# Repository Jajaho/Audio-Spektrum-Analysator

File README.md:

# Audio-Spektrum-Analysator
Analog audio spectrum analyzer with bar graph display.

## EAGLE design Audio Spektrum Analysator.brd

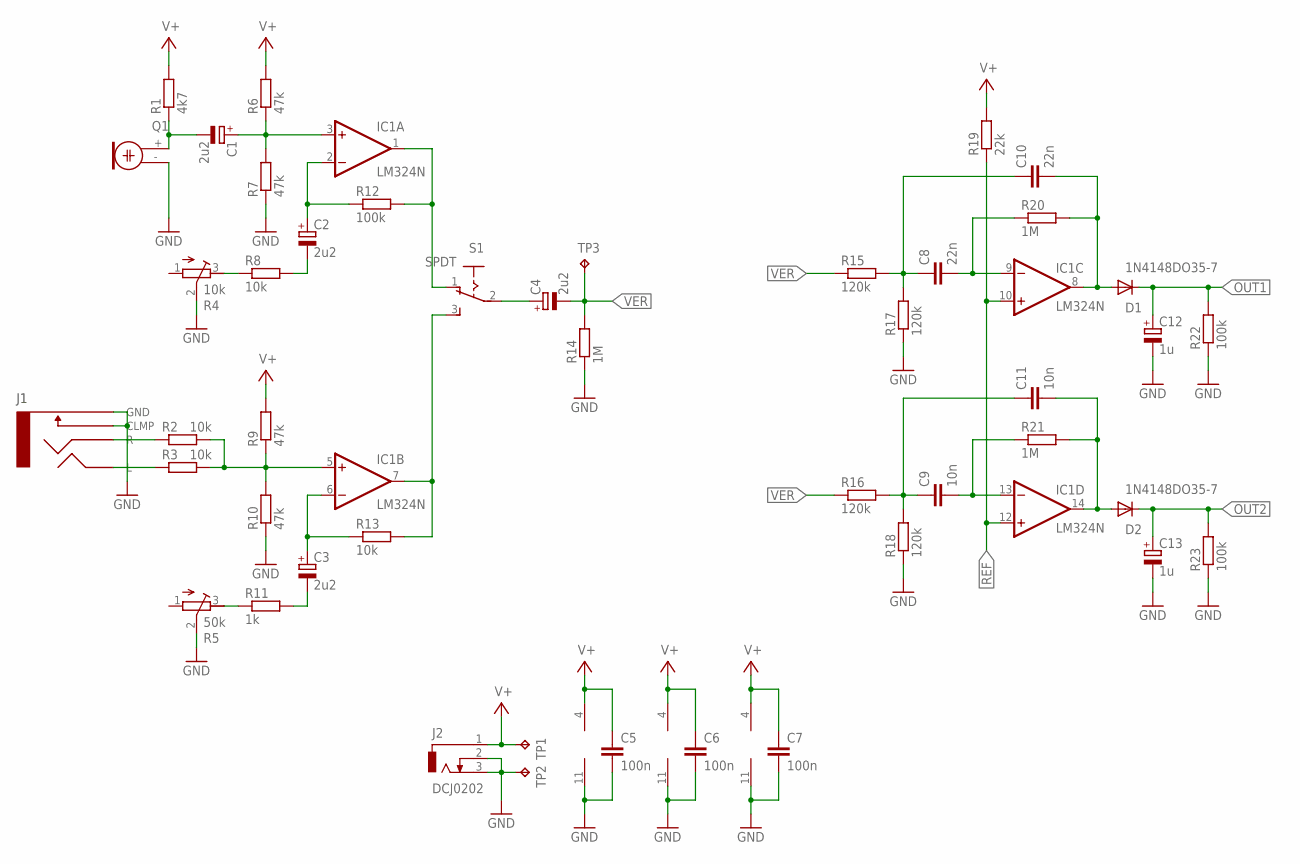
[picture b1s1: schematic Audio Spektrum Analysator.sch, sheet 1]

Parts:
C1, C2, C3, C4: 2u2; E2,5-5
C5, C6, C7: 100n; C050-024X044
C8, C10: 22n; C025-024X044
C9, C11: 10n; C025-024X044
C12, C13: 1u; E2,5-5
D1, D2: 1N4148DO35-7; DO35-7
IC1, IC2, IC3: LM324N; DIL14
J1: 2.5MM-AUXS; 2,5MM-AUX_JACK
J2: DCJ0202
Q1: ELECTRET; 9.7ELECTRET
R1: 4k7; 0207/7
R2, R3, R8, R13: 10k; 0207/7
R4: 10k; RTRIM64W
R5: 50k; RTRIM64W
R6, R7, R9, R10: 47k; 0207/7
R11: 1k; 0207/7
R12, R22, R23: 100k; 0207/7
R14, R20, R21: 1M; 0207/7
R15, R16, R17, R18: 120k; 0207/7
R19: 22k; 0207/7
S1: SPDT
TP1, TP2, TP3: TPPAD1-20; P1-20

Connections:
GND: C5.2, C6.2, C7.2, C12.-, C13.-, IC1.11 (V-), IC2.11 (V-), IC3.11 (V-), J1.1 (GND), J1.4 (CLMP), J2.2, J2.3, Q1.- (1), R4.2 (S), R5.2 (S), R7.1, R10.1, R14.1, R17.1, R18.1, R22.1, R23.1, TP2.TP; also elsewhere on the board
unnamed: J1.2 (R), R2.1
unnamed: J1.3 (L), R3.1
unnamed: IC1.5 (+IN), R2.2, R3.2, R9.1, R10.2
unnamed: C1.+, IC1.3 (+IN), R6.1, R7.2
unnamed: C2.+, IC1.2 (-IN), R12.1
unnamed: IC1.1 (OUT), R12.2, S1.1
unnamed: IC1.7 (OUT), R13.2, S1.3
unnamed: C4.+, S1.2
unnamed: C1.-, Q1.+ (2), R1.1
unnamed: C2.-, R8.2
unnamed: R4.3 (E), R8.1
unnamed: C3.+, IC1.6 (-IN), R13.1
unnamed: C3.-, R11.2
unnamed: R5.3 (E), R11.1
unnamed: C10.2, D1.A, IC1.8 (OUT), R20.2
unnamed: C8.2, IC1.9 (-IN), R20.1
unnamed: C8.1, C10.1, R15.2, R17.2
unnamed: C11.2, D2.A, IC1.14 (OUT), R21.2
unnamed: C9.2, IC1.13 (-IN), R21.1
unnamed: C9.1, C11.1, R16.2, R18.2
OUT1: C12.+, D1.C, R22.2; also elsewhere on the board
OUT2: C13.+, D2.C, R23.2; also elsewhere on the board
REF: IC1.10 (+IN), IC1.12 (+IN), R19.1; also elsewhere on the board
V+: C5.1, C6.1, C7.1, IC1.4 (V+), IC2.4 (V+), IC3.4 (V+), J2.1, R1.2, R6.2, R9.2, R19.2, TP1.TP; also elsewhere on the board
VER: C4.-, R14.2, R15.1, R16.1, TP3.TP; also elsewhere on the board

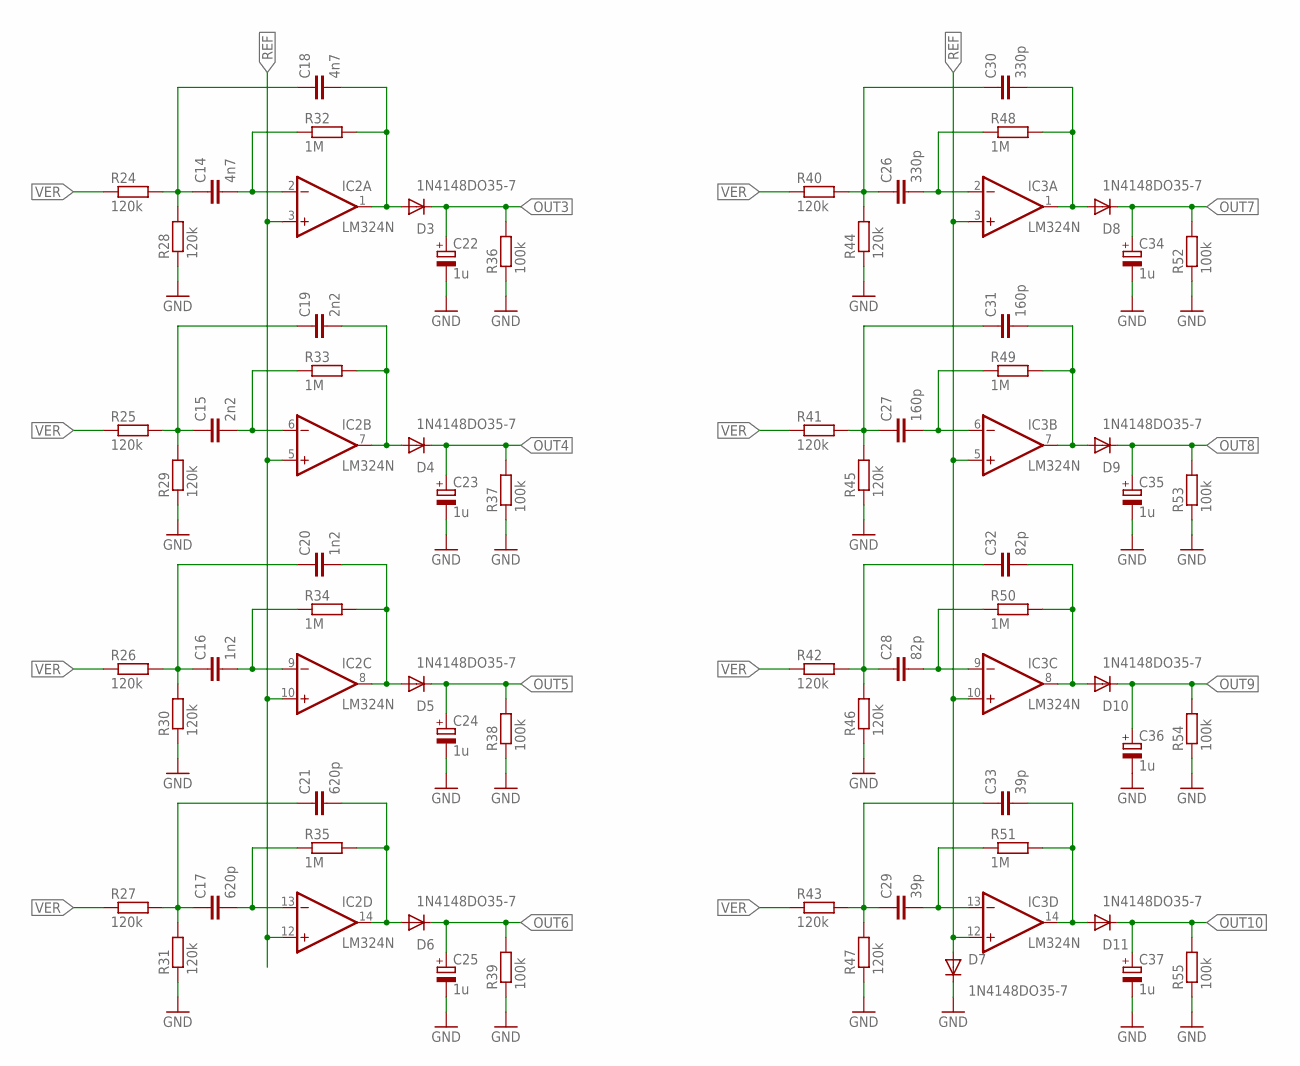
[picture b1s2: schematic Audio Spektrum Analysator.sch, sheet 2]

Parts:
C14, C18: 4n7; C025-024X044
C15, C19: 2n2; C025-024X044
C16, C20: 1n2; C025-024X044
C17, C21: 620p; C025-024X044
C22, C23, C24, C25, C34, C35, C36, C37: 1u; E2,5-5
C26, C30: 330p; C025-024X044
C27, C31: 160p; C025-024X044
C28, C32: 82p; C025-024X044
C29, C33: 39p; C025-024X044
D3, D4, D5, D6, D7, D8, D9, D10, D11: 1N4148DO35-7; DO35-7
IC2, IC3: LM324N; DIL14
R24, R25, R26, R27, R28, R29, R30, R31, R40, R41, R42, R43, R44, R45, R46, R47: 120k; 0207/7
R32, R33, R34, R35, R48, R49, R50, R51: 1M; 0207/7
R36, R37, R38, R39, R52, R53, R54, R55: 100k; 0207/7

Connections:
GND: C22.-, C23.-, C24.-, C25.-, C34.-, C35.-, C36.-, C37.-, D7.C, R28.1, R29.1, R30.1, R31.1, R36.1, R37.1, R38.1, R39.1, R44.1, R45.1, R46.1, R47.1, R52.1, R53.1, R54.1, R55.1; also elsewhere on the board
unnamed: C18.2, D3.A, IC2.1 (OUT), R32.2
unnamed: C14.2, IC2.2 (-IN), R32.1
unnamed: C21.2, D6.A, IC2.14 (OUT), R35.2
unnamed: C14.1, C18.1, R24.2, R28.2
unnamed: C19.2, D4.A, IC2.7 (OUT), R33.2
unnamed: C15.2, IC2.6 (-IN), R33.1
unnamed: C17.2, IC2.13 (-IN), R35.1
unnamed: C15.1, C19.1, R25.2, R29.2
unnamed: C20.2, D5.A, IC2.8 (OUT), R34.2
unnamed: C16.2, IC2.9 (-IN), R34.1
unnamed: C30.2, D8.A, IC3.1 (OUT), R48.2
unnamed: C16.1, C20.1, R26.2, R30.2
unnamed: C17.1, C21.1, R27.2, R31.2
unnamed: C26.2, IC3.2 (-IN), R48.1
unnamed: C26.1, C30.1, R40.2, R44.2
unnamed: C31.2, D9.A, IC3.7 (OUT), R49.2
unnamed: C27.2, IC3.6 (-IN), R49.1
unnamed: C27.1, C31.1, R41.2, R45.2
unnamed: C32.2, D10.A, IC3.8 (OUT), R50.2
unnamed: C28.2, IC3.9 (-IN), R50.1
unnamed: C28.1, C32.1, R42.2, R46.2
unnamed: C33.2, D11.A, IC3.14 (OUT), R51.2
unnamed: C29.2, IC3.13 (-IN), R51.1
unnamed: C29.1, C33.1, R43.2, R47.2
OUT3: C22.+, D3.C, R36.2; also elsewhere on the board
OUT4: C23.+, D4.C, R37.2; also elsewhere on the board
OUT5: C24.+, D5.C, R38.2; also elsewhere on the board
OUT6: C25.+, D6.C, R39.2; also elsewhere on the board
OUT7: C34.+, D8.C, R52.2; also elsewhere on the board
OUT8: C35.+, D9.C, R53.2; also elsewhere on the board
OUT9: C36.+, D10.C, R54.2; also elsewhere on the board
OUT10: C37.+, D11.C, R55.2; also elsewhere on the board
REF: D7.A, IC2.3 (+IN), IC2.5 (+IN), IC2.10 (+IN), IC2.12 (+IN), IC3.3 (+IN), IC3.5 (+IN), IC3.10 (+IN), IC3.12 (+IN); also elsewhere on the board
VER: R24.1, R25.1, R26.1, R27.1, R40.1, R41.1, R42.1, R43.1; also elsewhere on the board

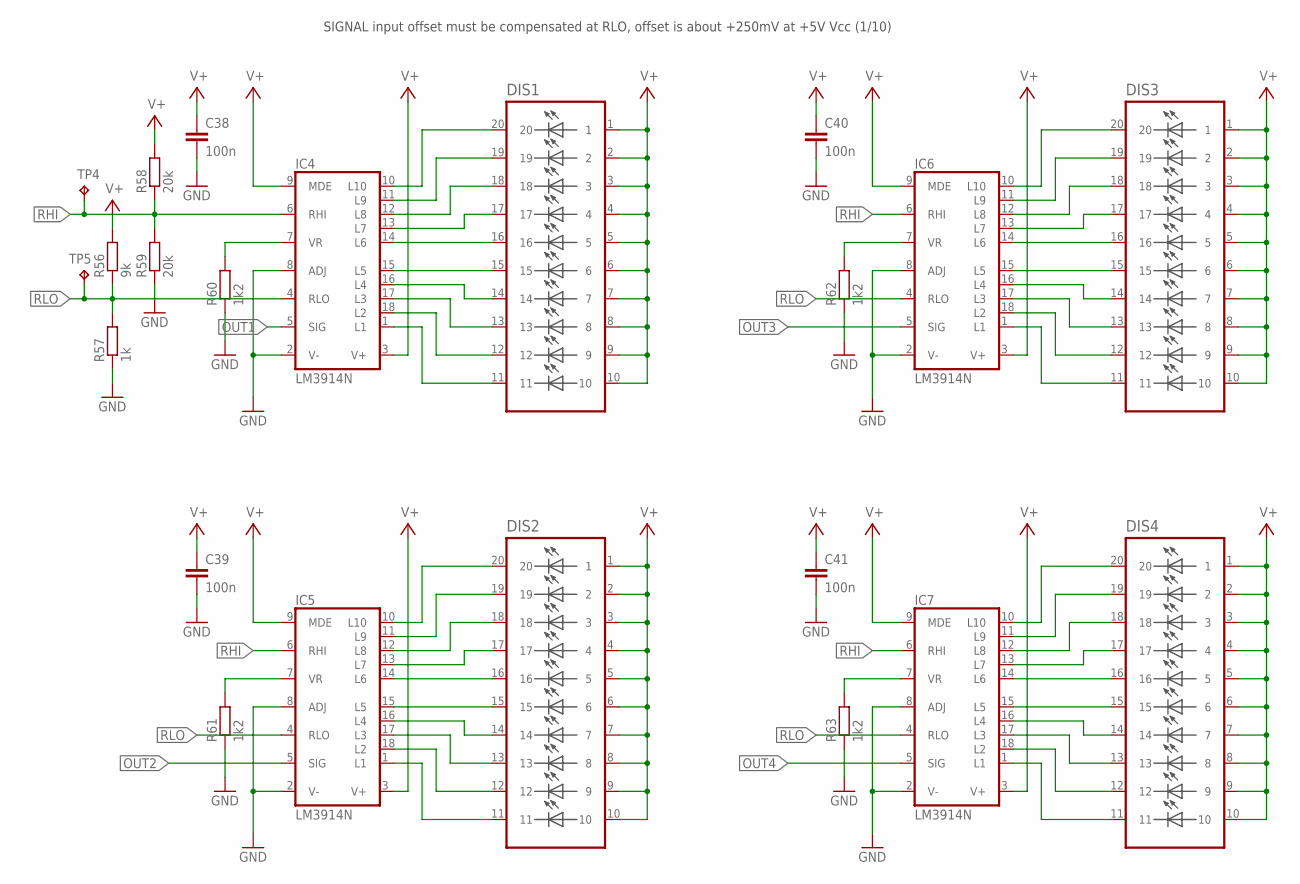
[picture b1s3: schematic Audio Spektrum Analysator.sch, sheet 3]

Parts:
C38, C39, C40, C41: 100n; C050-024X044
DIS1, DIS2, DIS3, DIS4: SHB10R
IC4, IC5, IC6, IC7: LM3914N; DIL18
R56: 9k; 0207/7
R57: 1k; 0207/7
R58, R59: 20k; 0207/7
R60, R61, R62, R63: 1k2; 0207/7
TP4, TP5: TPPAD1-20; P1-20

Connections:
GND: C38.2, C39.2, C40.2, C41.2, IC4.2 (V-), IC4.8 (ADJ), IC5.2 (V-), IC5.8 (ADJ), IC6.2 (V-), IC6.8 (ADJ), IC7.2 (V-), IC7.8 (ADJ), R57.1, R59.1, R60.1, R61.1, R62.1, R63.1; also elsewhere on the board
unnamed: DIS3.15, IC6.15 (L5)
unnamed: DIS3.14, IC6.16 (L4)
unnamed: DIS3.13, IC6.17 (L3)
unnamed: DIS3.12, IC6.18 (L2)
unnamed: DIS3.11, IC6.1 (L1)
unnamed: DIS3.16, IC6.14 (L6)
unnamed: DIS3.17, IC6.13 (L7)
unnamed: DIS3.18, IC6.12 (L8)
unnamed: DIS3.19, IC6.11 (L9)
unnamed: DIS3.20, IC6.10 (L10)
unnamed: IC6.7 (VR), R62.2
unnamed: IC5.7 (VR), R61.2
unnamed: DIS2.15, IC5.15 (L5)
unnamed: DIS2.14, IC5.16 (L4)
unnamed: DIS2.13, IC5.17 (L3)
unnamed: DIS2.12, IC5.18 (L2)
unnamed: DIS2.11, IC5.1 (L1)
unnamed: DIS2.16, IC5.14 (L6)
unnamed: DIS2.17, IC5.13 (L7)
unnamed: DIS2.18, IC5.12 (L8)
unnamed: DIS2.19, IC5.11 (L9)
unnamed: DIS2.20, IC5.10 (L10)
unnamed: IC7.7 (VR), R63.2
unnamed: DIS4.15, IC7.15 (L5)
unnamed: DIS4.14, IC7.16 (L4)
unnamed: DIS4.13, IC7.17 (L3)
unnamed: DIS4.12, IC7.18 (L2)
unnamed: DIS4.11, IC7.1 (L1)
unnamed: DIS4.16, IC7.14 (L6)
unnamed: DIS4.17, IC7.13 (L7)
unnamed: DIS4.18, IC7.12 (L8)
unnamed: DIS4.19, IC7.11 (L9)
unnamed: DIS4.20, IC7.10 (L10)
unnamed: DIS1.15, IC4.15 (L5)
unnamed: DIS1.14, IC4.16 (L4)
unnamed: DIS1.13, IC4.17 (L3)
unnamed: DIS1.12, IC4.18 (L2)
unnamed: DIS1.11, IC4.1 (L1)
unnamed: DIS1.16, IC4.14 (L6)
unnamed: DIS1.17, IC4.13 (L7)
unnamed: DIS1.18, IC4.12 (L8)
unnamed: DIS1.19, IC4.11 (L9)
unnamed: DIS1.20, IC4.10 (L10)
unnamed: IC4.7 (VR), R60.2
OUT1: IC4.5 (SIG); also elsewhere on the board
OUT2: IC5.5 (SIG); also elsewhere on the board
OUT3: IC6.5 (SIG); also elsewhere on the board
OUT4: IC7.5 (SIG); also elsewhere on the board
RHI: IC4.6 (RHI), IC5.6 (RHI), IC6.6 (RHI), IC7.6 (RHI), R58.1, R59.2, TP4.TP; also elsewhere on the board
RLO: IC4.4 (RLO), IC5.4 (RLO), IC6.4 (RLO), IC7.4 (RLO), R56.1, R57.2, TP5.TP; also elsewhere on the board
V+: C38.1, C39.1, C40.1, C41.1, DIS1.1, DIS1.2, DIS1.3, DIS1.4, DIS1.5, DIS1.6, DIS1.7, DIS1.8, DIS1.9, DIS1.10, DIS2.1, DIS2.2, DIS2.3, DIS2.4, DIS2.5, DIS2.6, DIS2.7, DIS2.8, DIS2.9, DIS2.10, DIS3.1, DIS3.2, DIS3.3, DIS3.4, DIS3.5, DIS3.6, DIS3.7, DIS3.8, DIS3.9, DIS3.10, DIS4.1, DIS4.2, DIS4.3, DIS4.4, DIS4.5, DIS4.6, DIS4.7, DIS4.8, DIS4.9, DIS4.10, IC4.3 (V+), IC4.9 (MDE), IC5.3 (V+), IC5.9 (MDE), IC6.3 (V+), IC6.9 (MDE), IC7.3 (V+), IC7.9 (MDE), R56.2, R58.2; also elsewhere on the board

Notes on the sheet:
SIGNAL input offset must be compensated at RLO, offset is about +250mV at +5V Vcc (1/10)

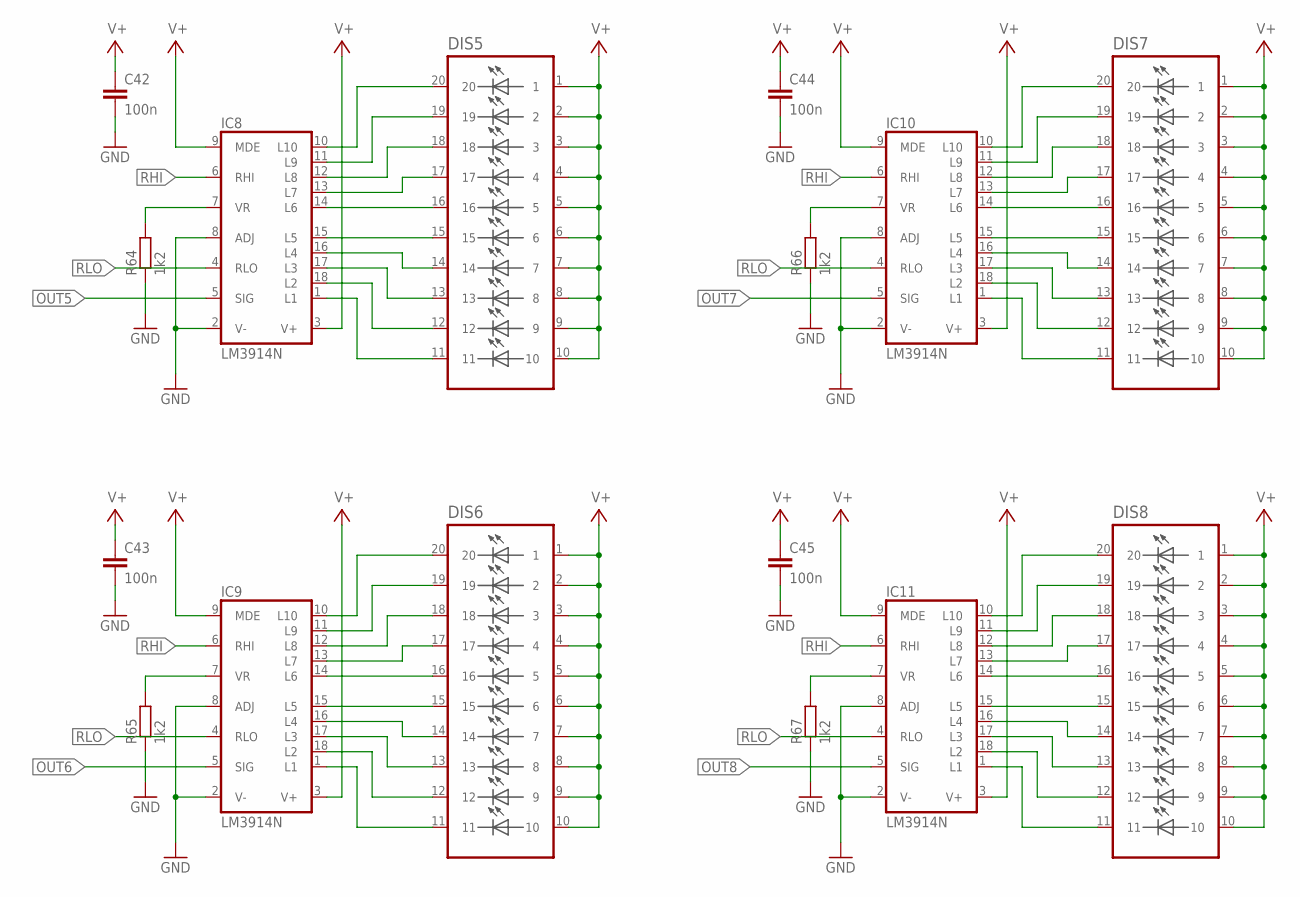
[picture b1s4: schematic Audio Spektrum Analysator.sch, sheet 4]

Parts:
C42, C43, C44, C45: 100n; C050-024X044
DIS5, DIS6, DIS7, DIS8: SHB10R
IC8, IC9, IC10, IC11: LM3914N; DIL18
R64, R65, R66, R67: 1k2; 0207/7

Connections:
GND: C42.2, C43.2, C44.2, C45.2, IC8.2 (V-), IC8.8 (ADJ), IC9.2 (V-), IC9.8 (ADJ), IC10.2 (V-), IC10.8 (ADJ), IC11.2 (V-), IC11.8 (ADJ), R64.1, R65.1, R66.1, R67.1; also elsewhere on the board
unnamed: IC8.7 (VR), R64.2
unnamed: IC10.7 (VR), R66.2
unnamed: IC9.7 (VR), R65.2
unnamed: DIS5.15, IC8.15 (L5)
unnamed: DIS5.14, IC8.16 (L4)
unnamed: DIS5.13, IC8.17 (L3)
unnamed: DIS5.12, IC8.18 (L2)
unnamed: DIS5.11, IC8.1 (L1)
unnamed: DIS5.16, IC8.14 (L6)
unnamed: DIS5.17, IC8.13 (L7)
unnamed: DIS5.18, IC8.12 (L8)
unnamed: DIS5.19, IC8.11 (L9)
unnamed: DIS5.20, IC8.10 (L10)
unnamed: IC11.7 (VR), R67.2
unnamed: DIS7.15, IC10.15 (L5)
unnamed: DIS7.14, IC10.16 (L4)
unnamed: DIS7.13, IC10.17 (L3)
unnamed: DIS7.12, IC10.18 (L2)
unnamed: DIS7.11, IC10.1 (L1)
unnamed: DIS7.16, IC10.14 (L6)
unnamed: DIS7.17, IC10.13 (L7)
unnamed: DIS7.18, IC10.12 (L8)
unnamed: DIS7.19, IC10.11 (L9)
unnamed: DIS7.20, IC10.10 (L10)
unnamed: DIS6.15, IC9.15 (L5)
unnamed: DIS6.14, IC9.16 (L4)
unnamed: DIS6.13, IC9.17 (L3)
unnamed: DIS6.12, IC9.18 (L2)
unnamed: DIS6.11, IC9.1 (L1)
unnamed: DIS6.16, IC9.14 (L6)
unnamed: DIS6.17, IC9.13 (L7)
unnamed: DIS6.18, IC9.12 (L8)
unnamed: DIS6.19, IC9.11 (L9)
unnamed: DIS6.20, IC9.10 (L10)
unnamed: DIS8.15, IC11.15 (L5)
unnamed: DIS8.14, IC11.16 (L4)
unnamed: DIS8.13, IC11.17 (L3)
unnamed: DIS8.12, IC11.18 (L2)
unnamed: DIS8.11, IC11.1 (L1)
unnamed: DIS8.16, IC11.14 (L6)
unnamed: DIS8.17, IC11.13 (L7)
unnamed: DIS8.18, IC11.12 (L8)
unnamed: DIS8.19, IC11.11 (L9)
unnamed: DIS8.20, IC11.10 (L10)
OUT5: IC8.5 (SIG); also elsewhere on the board
OUT6: IC9.5 (SIG); also elsewhere on the board
OUT7: IC10.5 (SIG); also elsewhere on the board
OUT8: IC11.5 (SIG); also elsewhere on the board
RHI: IC8.6 (RHI), IC9.6 (RHI), IC10.6 (RHI), IC11.6 (RHI); also elsewhere on the board
RLO: IC8.4 (RLO), IC9.4 (RLO), IC10.4 (RLO), IC11.4 (RLO); also elsewhere on the board
V+: C42.1, C43.1, C44.1, C45.1, DIS5.1, DIS5.2, DIS5.3, DIS5.4, DIS5.5, DIS5.6, DIS5.7, DIS5.8, DIS5.9, DIS5.10, DIS6.1, DIS6.2, DIS6.3, DIS6.4, DIS6.5, DIS6.6, DIS6.7, DIS6.8, DIS6.9, DIS6.10, DIS7.1, DIS7.2, DIS7.3, DIS7.4, DIS7.5, DIS7.6, DIS7.7, DIS7.8, DIS7.9, DIS7.10, DIS8.1, DIS8.2, DIS8.3, DIS8.4, DIS8.5, DIS8.6, DIS8.7, DIS8.8, DIS8.9, DIS8.10, IC8.3 (V+), IC8.9 (MDE), IC9.3 (V+), IC9.9 (MDE), IC10.3 (V+), IC10.9 (MDE), IC11.3 (V+), IC11.9 (MDE); also elsewhere on the board

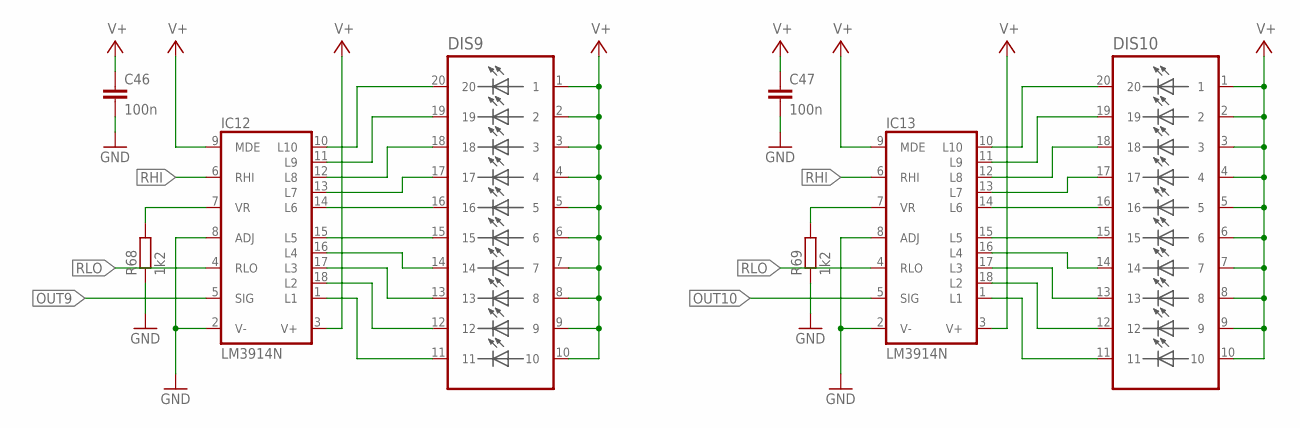
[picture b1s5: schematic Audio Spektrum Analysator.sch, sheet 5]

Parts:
C46, C47: 100n; C050-024X044
DIS9, DIS10: SHB10R
IC12, IC13: LM3914N; DIL18
R68, R69: 1k2; 0207/7

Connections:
GND: C46.2, C47.2, IC12.2 (V-), IC12.8 (ADJ), IC13.2 (V-), IC13.8 (ADJ), R68.1, R69.1; also elsewhere on the board
unnamed: DIS9.15, IC12.15 (L5)
unnamed: DIS9.14, IC12.16 (L4)
unnamed: DIS9.13, IC12.17 (L3)
unnamed: DIS9.12, IC12.18 (L2)
unnamed: DIS9.11, IC12.1 (L1)
unnamed: DIS9.16, IC12.14 (L6)
unnamed: DIS9.17, IC12.13 (L7)
unnamed: DIS9.18, IC12.12 (L8)
unnamed: DIS9.19, IC12.11 (L9)
unnamed: IC12.7 (VR), R68.2
unnamed: IC13.7 (VR), R69.2
unnamed: DIS9.20, IC12.10 (L10)
unnamed: DIS10.15, IC13.15 (L5)
unnamed: DIS10.14, IC13.16 (L4)
unnamed: DIS10.13, IC13.17 (L3)
unnamed: DIS10.12, IC13.18 (L2)
unnamed: DIS10.11, IC13.1 (L1)
unnamed: DIS10.16, IC13.14 (L6)
unnamed: DIS10.17, IC13.13 (L7)
unnamed: DIS10.18, IC13.12 (L8)
unnamed: DIS10.19, IC13.11 (L9)
unnamed: DIS10.20, IC13.10 (L10)
OUT9: IC12.5 (SIG); also elsewhere on the board
OUT10: IC13.5 (SIG); also elsewhere on the board
RHI: IC12.6 (RHI), IC13.6 (RHI); also elsewhere on the board
RLO: IC12.4 (RLO), IC13.4 (RLO); also elsewhere on the board
V+: C46.1, C47.1, DIS9.1, DIS9.2, DIS9.3, DIS9.4, DIS9.5, DIS9.6, DIS9.7, DIS9.8, DIS9.9, DIS9.10, DIS10.1, DIS10.2, DIS10.3, DIS10.4, DIS10.5, DIS10.6, DIS10.7, DIS10.8, DIS10.9, DIS10.10, IC12.3 (V+), IC12.9 (MDE), IC13.3 (V+), IC13.9 (MDE); also elsewhere on the board

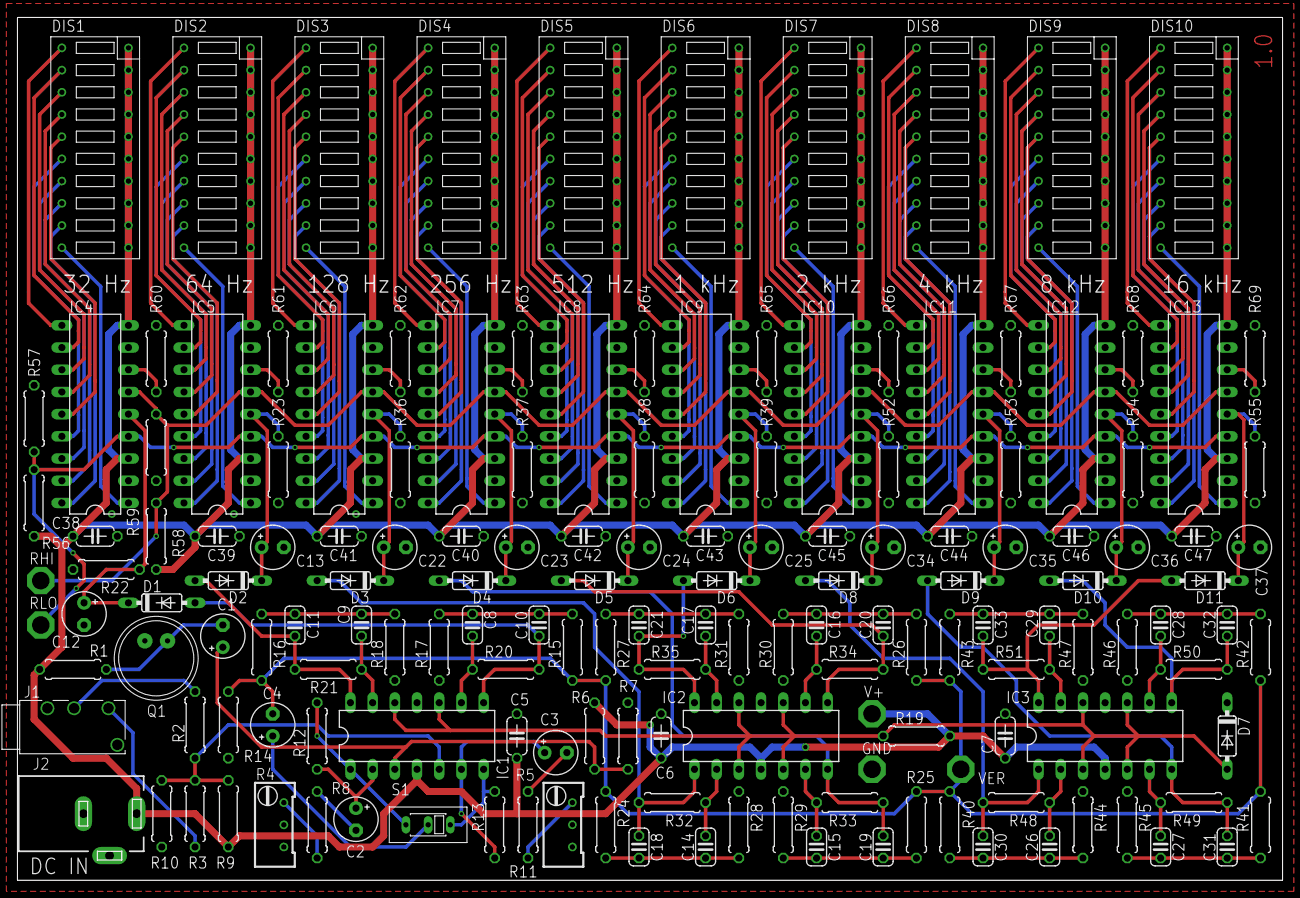
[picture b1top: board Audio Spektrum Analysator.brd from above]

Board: 2 copper layers, 144.8 x 98.7 mm, 159 parts (0 on the bottom side), 170 nets.

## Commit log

2018-07-13 Add new file
2018-07-15 started layout
2018-07-15 connected bandpass
2018-07-15 moved LM324
2018-07-15 created final shape
2018-07-16 moved caps and co to top side
2018-07-17 replaced dc blocking caps, print back side, added dc jack
2018-07-18 updated to eagle 9.1.1
2018-07-21 renamed
2018-07-21 moved more names
2018-07-21 moved names
2018-07-22 worked on electret mic amp
2018-07-22 removed layers
2018-07-29 edited preamp
2018-07-29 edited reference circuit of LM3916s
2018-07-29 started connecting Lm3916s
2018-07-30 removed layers, further connected LM3916s
2018-07-30 added RLO offest compensation in the schematic
2018-07-30 implemented offset compensation circuit in layout
2018-07-31 swapped poti
2018-08-05 finished layout
2018-08-06 moved names, added testpoints
2018-08-08 replaced s1
2018-08-10 Ich habe fertig V1.0
2018-08-11 changed 2.5mm jack holes
2023-07-04 Adds pdf, Removes unwanted layers
